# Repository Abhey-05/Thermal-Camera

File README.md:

<h1>
  Thermal Camera
</h1>
A compact, low-cost thermal imaging solution built for diagnostic, repair, and monitoring applications in electronics, industrial safety, and embedded systems. Unlike commercial thermal cameras that are often expensive, this DIY thermal imager is designed using readily available and affordable components, making it accessible for students, hobbyists, and engineers.

Thermal cameras play a critical role in detecting temperature anomalies, benchmarking heat performance, and assisting in electronic hardware debugging. Commonly used in defense, predictive maintenance, and the repair industry, thermal imaging enables faster and safer identification of faults such as short circuits or overheating components. Our project aims to replicate these capabilities at a fraction of the market cost.

<h2>Project Workflow </h2>

We began by understanding the working principles of thermal cameras and the core requirements of a low-cost system. The MLX90640 thermal sensor was selected for its high sensitivity and compact resolution, while the 2.4” TFT display offered a visually rich and user-friendly interface.

We wrote firmware from scratch to handle thermal data acquisition, color mapping, and display control using an ESP32 microcontroller. All SPI and I2C communication protocols were manually configured and tested for stability. We then implemented SD card image storage and added support for selectable color palettes and refresh rates.

The enclosure and power management were developed in parallel. A custom battery management system was integrated to allow portability, and the housing was designed to be compact yet thermally stable. The complete schematic and PCB were designed in KiCad.

<h2>
Features:
</h2>

- Image Sensor Resolution: 32×24 pixels
- Field of View (FoV): 55° × 35°
- Temperature Measurement Range: -40°C to 300°C
- Operating Temperature Range: -40°C to 85°C
- Adjustable Refresh Rate: 4 Hz to 32 Hz
- Color Palettes: 10 selectable thermal color schemes
- Display: 2.4" TFT screen with 320×240 resolution
- Storage: Supports saving thermal images to SD card
- Power: Built-in rechargeable battery with charging circuit

<h2>Schematic</h2>

<h2>PCB Layout </h2>

<h2>Setup</h2>

<h2> Working Video </h2>

https://github.com/user-attachments/assets/c0b89b00-765c-46c9-96d5-a79226db0dfd

https://github.com/user-attachments/assets/fa7a4603-ffcd-4ff7-a3ee-2d5423cac2e8

<h2>Applications</h2>

- Electronics repair and thermal diagnostics
- Industrial safety monitoring
- DIY electronics and embedded systems projects
- Educational use for temperature visualization

<h2>Challenges Faced</h2>
 
- Occasional screen lag during rapid refresh.
- Difficulty in storing data reliably on the SD card due to SPI timing issues.
- Display showed only half-screen output initially, resolved through pin remapping and timing adjustments.

<h2>Team Members</h2>

- Abhey Garg (EE23BTECH11202)
- Chirag Garg (EE23BTECH11206)
- Prashant Maurya (EE23BTECH11218)
- Preetam (EE23BTECH11221)
- Sasa Mardi (EE23BTECH11222)

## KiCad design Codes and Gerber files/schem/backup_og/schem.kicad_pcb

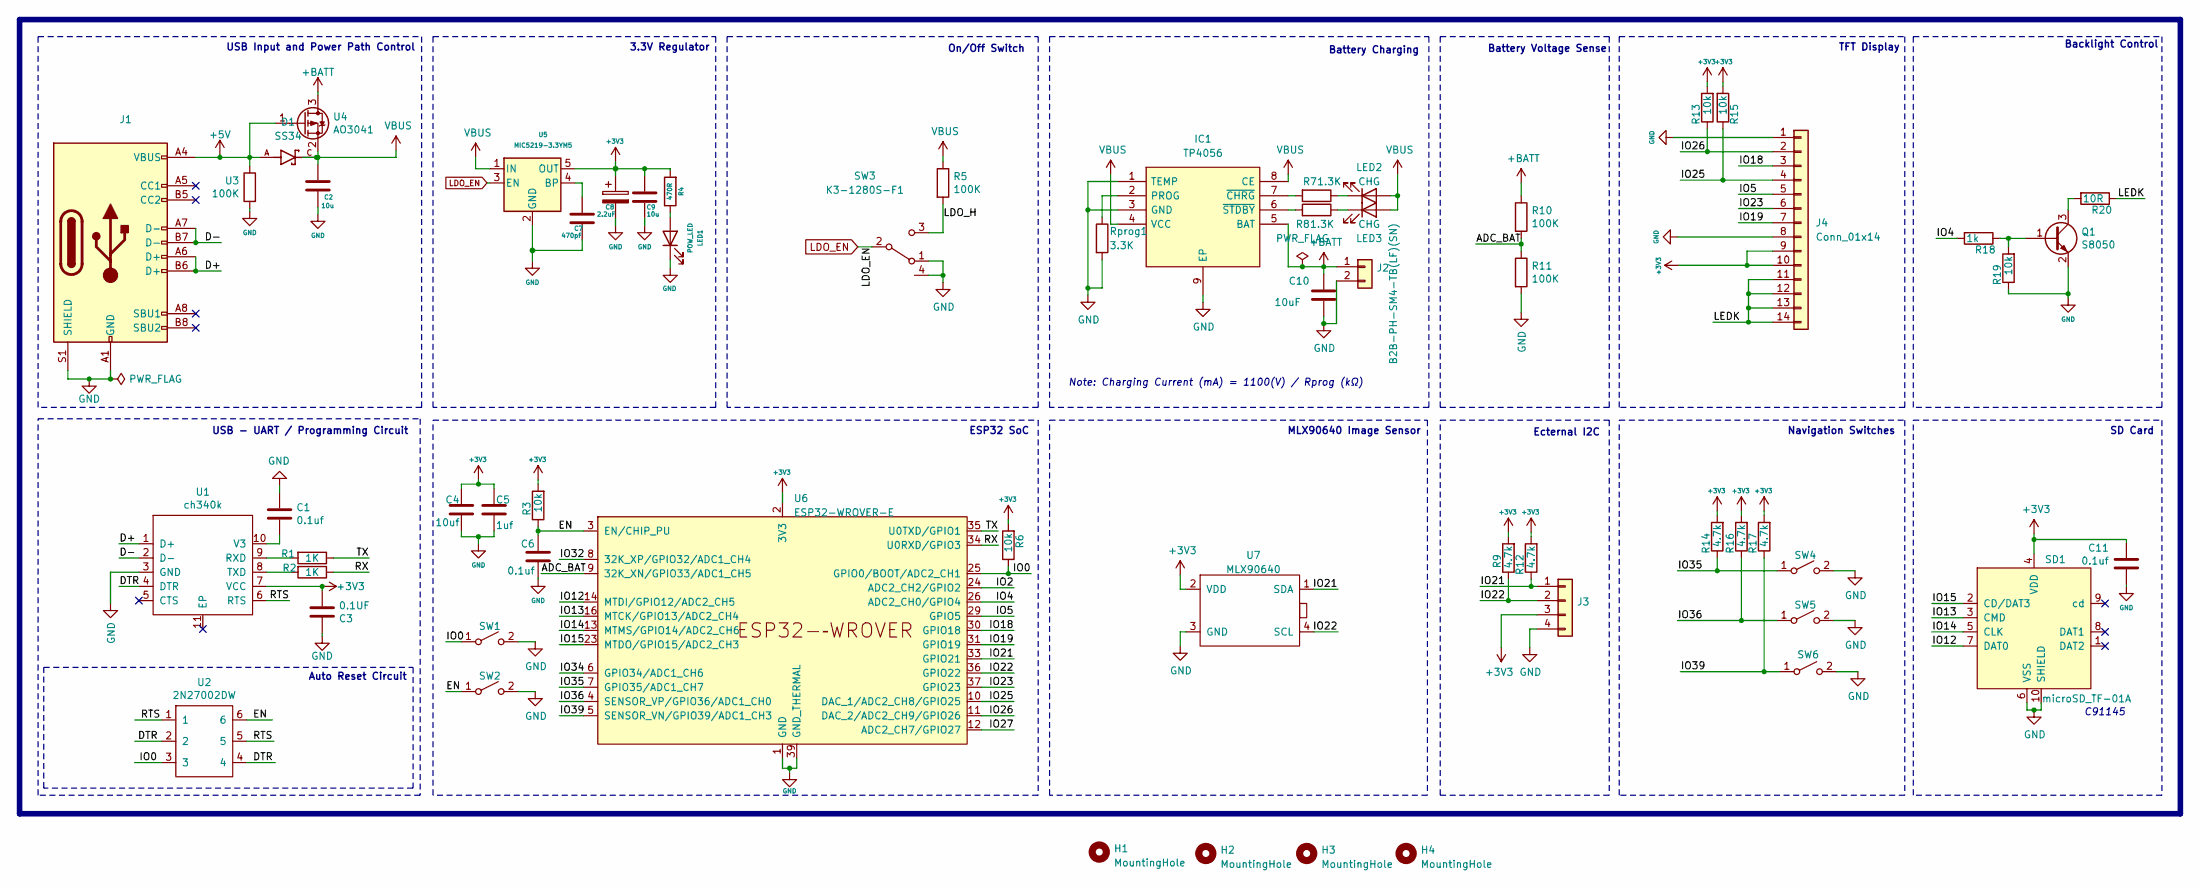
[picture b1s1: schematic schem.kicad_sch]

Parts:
C1, C6, C11: 0.1uf; C_0603_1608Metric
C2, C9: 10u; C_0603_1608Metric
C3: 0.1UF; C_0603_1608Metric
C4: 10uf; C_0603_1608Metric
C5: 1uf; C_0603_1608Metric
C7: 470pF; C_0603_1608Metric
C8: 2.2uF; C_0805_2012Metric
C10: 10uF; C_0603_1608Metric
D1: SS34; SS34_DIODE_NEW; PARTREV 31 Aug 2016
H1, H2, H3, H4: MountingHole; MountingHole_2.2mm_M2_ISO7380_Pad
IC1: TP4056; TP4056_SOP127P600X175-9N_TC; Manufacturer_Part_Number TP4056-42-ESOP8
J1: USB_C_Receptacle_USB2.0; USB_C_Receptacle_HRO_TYPE-C-31-M-12
J2: B2B-PH-SM4-TB(LF)(SN); JST_PH_B2B-PH-SM4-TB_1x02-1MP_P2.00mm_Vertical
J3: Stemma; JST_PH_B4B-PH-K_1x04_P2.00mm_Vertical
J4: Conn_01x14; PinSocket_1x14_P2.54mm_Vertical
LED1: POW_LED; LED_0603_1608Metric
LED2, LED3: CHG; LED_0603_1608Metric
Q1: S8050; TRANS_SS8050-G_TC
R1, R2: 1K; R_0603_1608Metric
R3, R6, R13, R15, R19: 10k; R_0603_1608Metric
R4: 470R; R_0603_1608Metric
R5, R10, R11: 100K; R_0603_1608Metric
R7, R8: 1.3K; R_0603_1608Metric
R9, R12, R14, R16, R17: 4.7k; R_0603_1608Metric
R18: 1k; R_0603_1608Metric
R20: 10R; R_0805_2012Metric
Rprog1: 3.3K; R_0603_1608Metric
SD1: microSD_TF-01A; sdcard_reader_TC
SW1, SW2: TS-1088R-02526; 2_TACTILE
SW3: K3-1280S-F1; slide_switch_TC
SW4, SW5, SW6: TS-1088R-02526; 4_TERMINAL_SWITCH_TC
U1: ch340k; ch340k_TC
U2: 2N27002DW; 2N7002DW_SOT363_TC
U3: 100K; R_0603_1608Metric
U4: AO3041; AO3401_SOT23_TC
U5: MIC5219-3.3YM5; MIC5219_SOT95P280X145-5N_TC
U6: ESP32-WROVER-E; ESP32WROVEREN8R8_TC
U7: MLX90640; MLX90640_ESFBAB000SP_TC

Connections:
+3V3: C3.2, C4.1, C5.1, C8.1, C9.1, C11.1, J3.3, J4.9, J4.10, R3.2, R4.2, R6.2, R9.2, R12.2, R13.2, R14.2, R15.2, R16.2, R17.2, SD1.4 (VDD), U1.7 (VCC), U5.5 (OUT), U6.2 (3V3), U7.2 (VDD)
+5V: D1.A, J1.A4 (VBUS), J1.A9 (VBUS), J1.B4 (VBUS), J1.B9 (VBUS), U3.1, U4.1 (G)
+BATT: C10.1, IC1.5 (BAT), J2.1, R10.1, U4.3 (D)
/ADC_BAT: R10.2, R11.1, U6.9 (32K_XN/GPIO33/ADC1_CH5)
/D+: J1.A6 (D+), J1.B6 (D+), U1.1 (D+)
/D-: J1.A7 (D-), J1.B7 (D-), U1.2 (D-)
/DTR: U1.4 (DTR), U2.2, U2.4
/EN: C6.1, R3.1, SW2.1 (A), U2.6, U6.3 (EN/CHIP_PU)
/IO0: R6.1, SW1.1 (A), U2.3, U6.25 (GPIO0/BOOT/ADC2_CH1)
/IO2: U6.24 (ADC2_CH2/GPIO2)
/IO4: R18.2, U6.26 (ADC2_CH0/GPIO4)
/IO5: J4.5, U6.29 (GPIO5)
/IO12: SD1.7 (DAT0), U6.14 (MTDI/GPIO12/ADC2_CH5)
/IO13: SD1.3 (CMD), U6.16 (MTCK/GPIO13/ADC2_CH4)
/IO14: SD1.5 (CLK), U6.13 (MTMS/GPIO14/ADC2_CH6)
/IO15: SD1.2 (CD/DAT3), U6.23 (MTDO/GPIO15/ADC2_CH3)
/IO18: J4.3, U6.30 (GPIO18)
/IO19: J4.7, U6.31 (GPIO19)
/IO21: J3.1, R12.1, U6.33 (GPIO21), U7.1 (SDA)
/IO22: J3.2, R9.1, U6.36 (GPIO22), U7.4 (SCL)
/IO23: J4.6, U6.37 (GPIO23)
/IO25: J4.4, R15.1, U6.10 (DAC_1/ADC2_CH8/GPIO25)
/IO26: J4.2, R13.1, U6.11 (DAC_2/ADC2_CH9/GPIO26)
/IO27: U6.12 (ADC2_CH7/GPIO27)
/IO32: U6.8 (32K_XP/GPIO32/ADC1_CH4)
/IO34: U6.6 (GPIO34/ADC1_CH6)
/IO35: R14.1, SW4.1 (A), U6.7 (GPIO35/ADC1_CH7)
/IO36: R16.1, SW5.1 (A), U6.4 (SENSOR_VP/GPIO36/ADC1_CH0)
/IO39: R17.1, SW6.1 (A), U6.5 (SENSOR_VN/GPIO39/ADC1_CH3)
/LDO_H: R5.2, SW3.3 (C)
/LEDK: J4.11, J4.12, J4.13, J4.14, R20.1
/RTS: U1.6 (RTS), U2.1, U2.5
/RX: R2.1, U6.34 (U0RXD/GPIO3)
/TX: R1.1, U6.35 (U0TXD/GPIO1)
GND: C1.1, C2.2, C3.1, C4.2, C5.2, C6.2, C7.2, C8.2, C9.2, C10.2, C11.2, IC1.1 (TEMP), IC1.3 (GND), IC1.9 (EP), J1.A1 (GND), J1.A12 (GND), J1.B1 (GND), J1.B12 (GND), J1.S1 (SHIELD), J2.2, J3.4, J4.1, J4.8, LED1.1 (K), Q1.2 (B), R11.2, R19.1, Rprog1.2, SD1.6 (VSS), SD1.10 (SHIELD), SW1.2 (B), SW2.2 (B), SW3.1 (A), SW3.4, SW4.2 (B), SW5.2 (B), SW6.2 (B), U1.3 (GND), U3.2, U5.2 (GND), U6.1 (GND), U6.15 (GND), U6.38 (GND), U6.39 (GND_THERMAL), U7.3 (GND)
LDO_EN: SW3.2 (B), U5.3 (EN)
unnamed: IC1.2 (PROG), Rprog1.1
unnamed: IC1.7 (~CHRG), R7.2
unnamed: IC1.6 (~STDBY), R8.2
unnamed: LED1.2 (A), R4.1
unnamed: LED2.1 (K), R7.1
unnamed: LED3.1 (K), R8.1
unnamed: Q1.3 (C), R20.2
unnamed: Q1.1 (E), R18.1, R19.2
unnamed: R1.2, U1.9 (RXD)
unnamed: R2.2, U1.8 (TXD)
unnamed: C1.2, U1.10 (V3)
unnamed: C7.1, U5.4 (BP)
VBUS: C2.1, D1.C, IC1.4 (VCC), IC1.8 (CE), LED2.2 (A), LED3.2 (A), R5.1, U4.2 (S), U5.1 (IN)

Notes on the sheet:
Note: Charging Current (mA) = 1100(V) / Rprog (kΩ)
On/Off Switch
USB - UART / Programming Circuit
USB Input and Power Path Control
Battery Voltage Sense
Ecternal I2C
Battery Charging
Navigation Switches
Backlight Control
MLX90640 Image Sensor
C91145
3.3V Regulator
Auto Reset Circuit
TFT Display
ESP32 SoC
SD Card

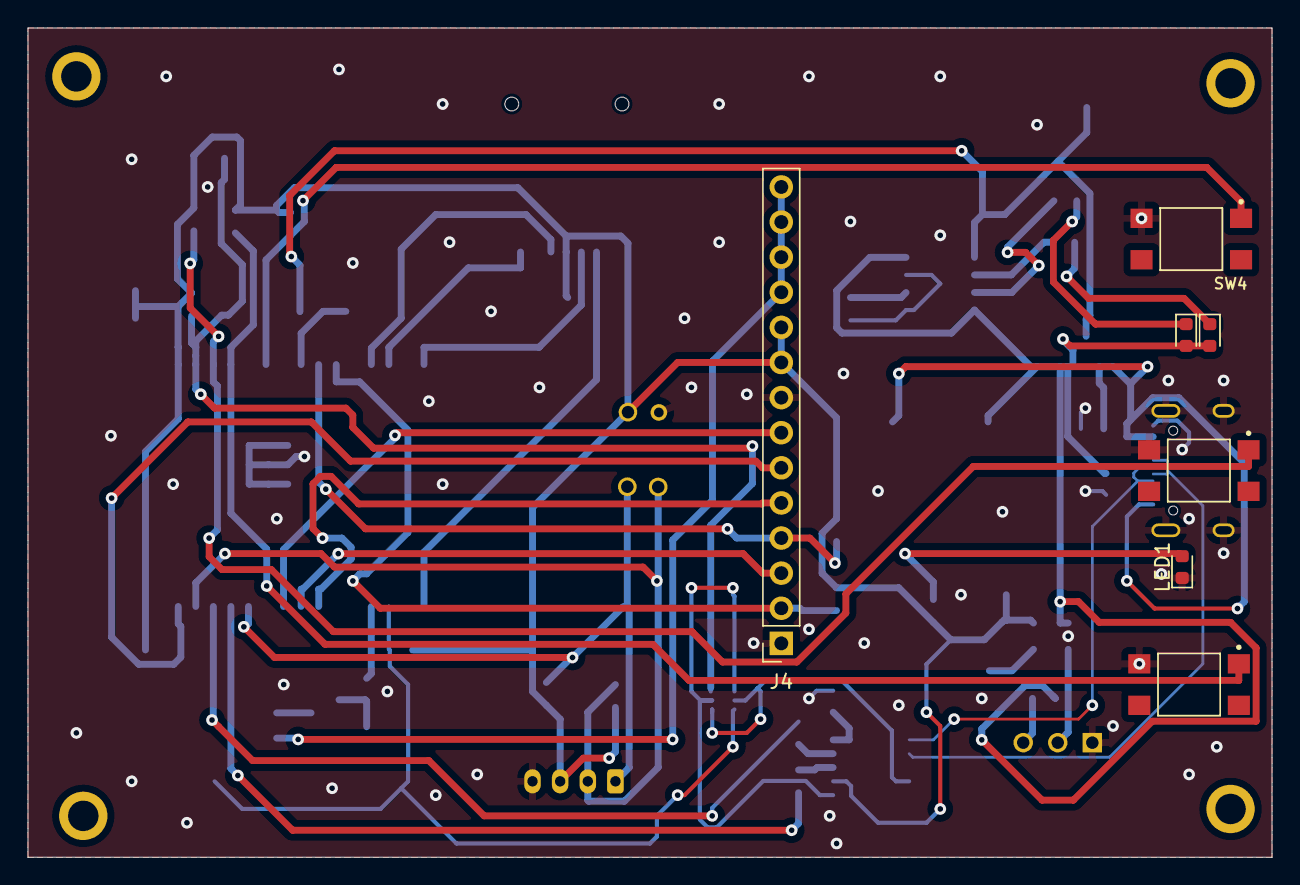
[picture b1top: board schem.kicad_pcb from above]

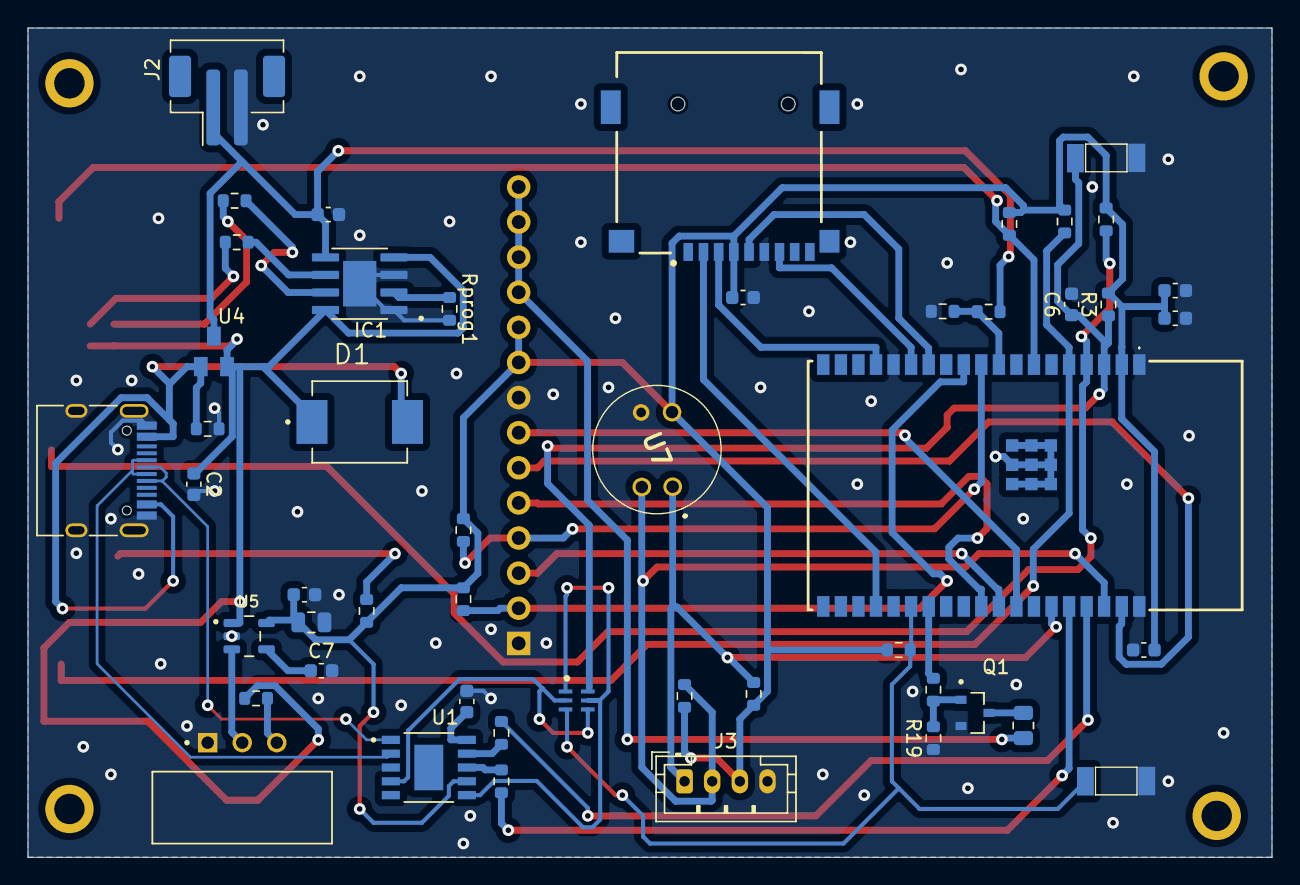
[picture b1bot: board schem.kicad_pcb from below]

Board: 2 copper layers, 90.0 x 60.0 mm, 60 parts (49 on the bottom side), 45 nets.

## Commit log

2025-04-17 Create sample
2025-05-01 Create a
2025-06-22 Rename Thermal_Camera Schematics.png to Schematic
2025-06-22 Rename Schematic to Schematic.png
2025-06-22 Rename Therml Camera (1).pptx to Thermal Camera.pptx
2025-06-22 Rename WhatsApp Image 2025-06-22 at 16.25.18.jpeg to Schematic.jpeg
2025-06-22 Rename Thermal_Camera_Design.pdf to Modules Working.pdf
